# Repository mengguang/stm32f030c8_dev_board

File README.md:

# stm32f030c8_dev_board
stm32f030c8t6 development board.

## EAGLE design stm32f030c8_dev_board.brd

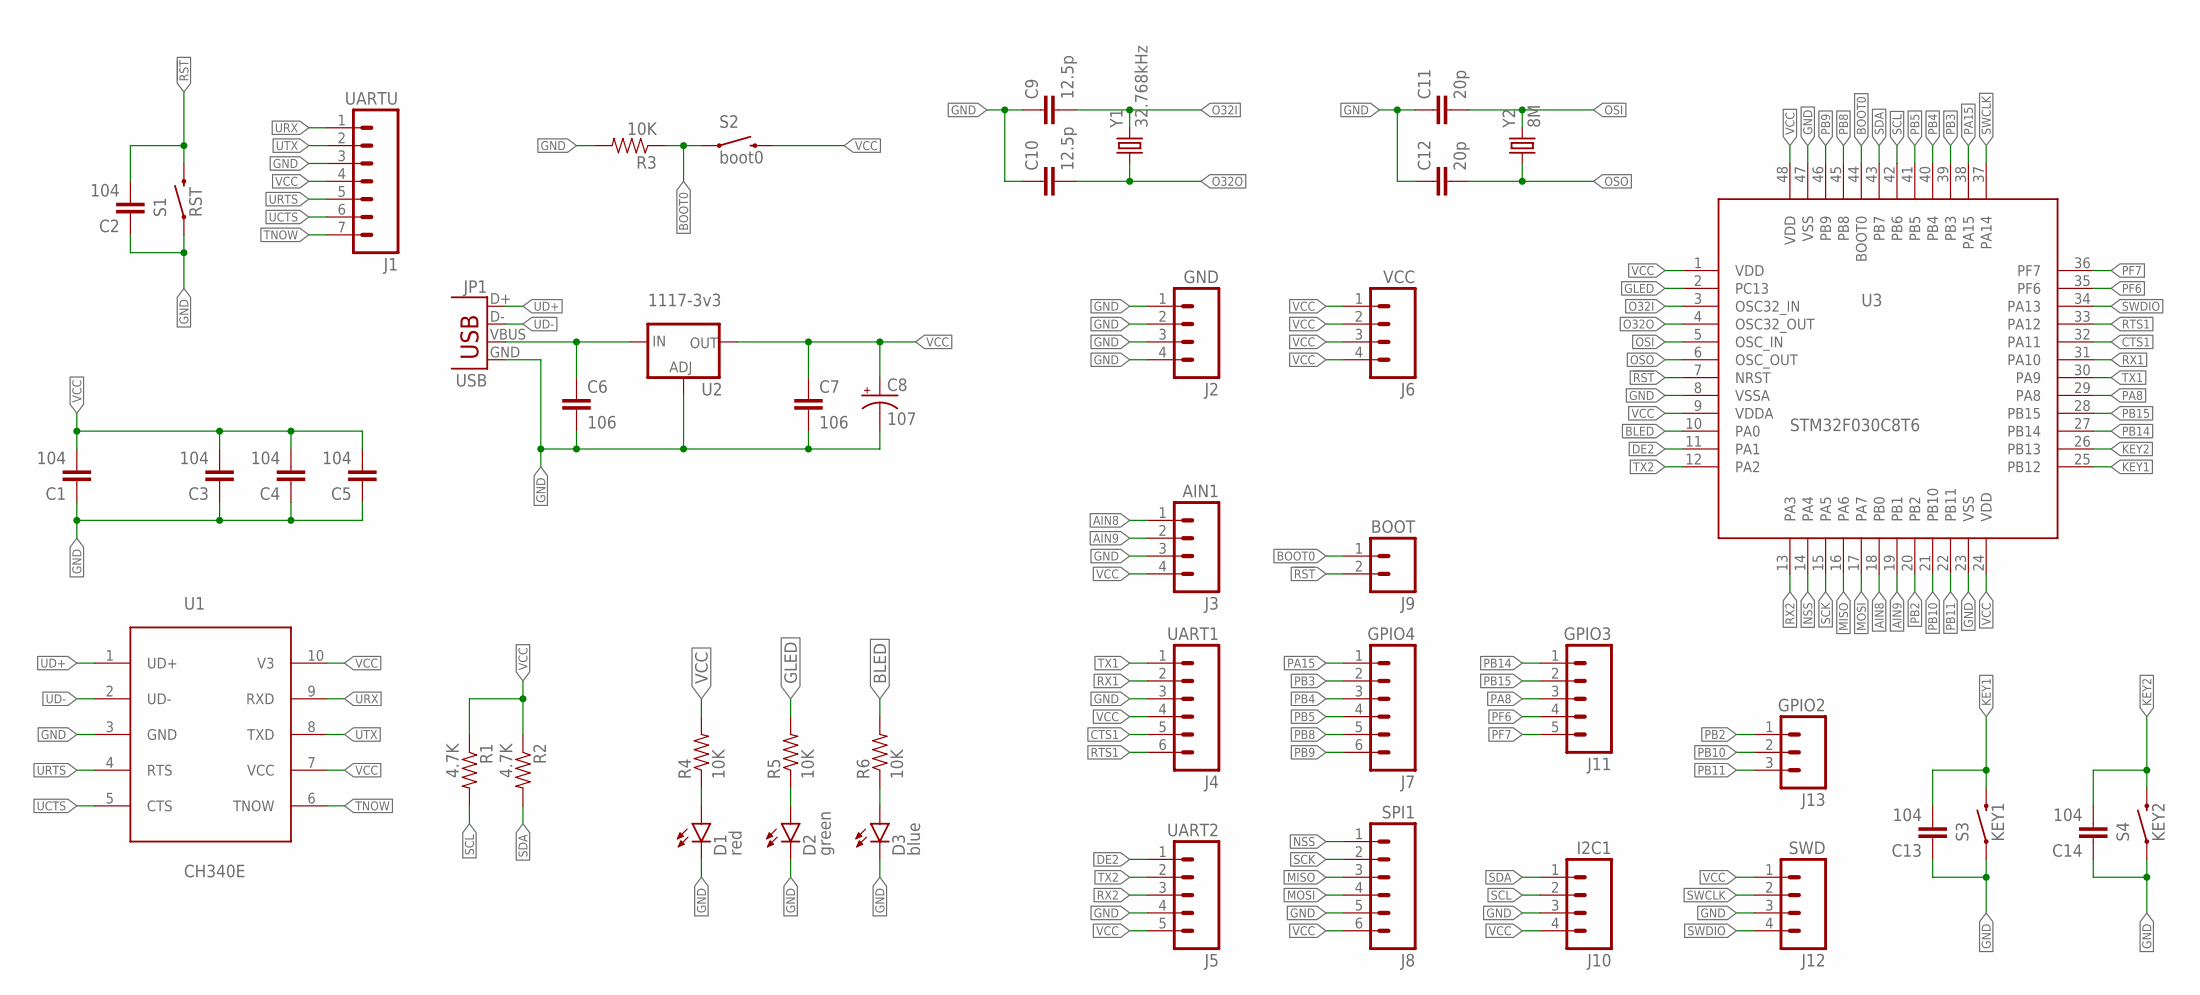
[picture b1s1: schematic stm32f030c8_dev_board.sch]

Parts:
C1, C2, C3, C4, C5, C13, C14: 104; C0402
C6, C7: 106; 0603-CAP
C8: 107; EIA3528
C9, C10: 12.5p; C0402
C11, C12: 20p; C0402
D1: red; LED-0603-SEEED
D2: green; LED-0603-SEEED
D3: blue; LED-0603-SEEED
J1: UARTU; 1X07_NO_SILK
J2: GND; 1X04_NO_SILK
J3: AIN1; 1X04_NO_SILK
J4: UART1; 1X06_NO_SILK
J5: UART2; 1X05_NO_SILK
J6: VCC; 1X04_NO_SILK
J7: GPIO4; 1X06_NO_SILK
J8: SPI1; 1X06_NO_SILK
J9: BOOT; 1X02_NO_SILK
J10: I2C1; 1X04_NO_SILK
J11: GPIO3; 1X05_NO_SILK
J12: SWD; 1X04_NO_SILK
J13: GPIO2; 1X03_NO_SILK
JP1: USB; MICROUSB-U-F-M5DD-Y-1
R1, R2: 4.7K; R0402
R3, R4, R5, R6: 10K; R0402
S1: RST; TACTILE-PTH
S2: boot0; TACTILE-PTH
S3: KEY1; TACTILE-PTH
S4: KEY2; TACTILE-PTH
U1: CH340E; MSOP10
U2: 1117-3v3; SOT223
U3: STM32F030C8T6; QFP50P900X900X160-48N
Y1: 32.768kHz; TC26H
Y2: 8M; HC49US

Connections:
!RST: C2.2, J9.2, S1.3 (2), U3.7 (NRST)
AIN8: J3.1, U3.18 (PB0)
AIN9: J3.2, U3.19 (PB1)
BLED: R6.2, U3.10 (PA0)
BOOT0: J9.1, R3.1, S2.1, U3.44 (BOOT0)
CTS1: J4.5, U3.32 (PA11)
DE2: J5.1, U3.11 (PA1)
GLED: R5.2, U3.2 (PC13)
GND: C1.1, C2.1, C3.1, C4.1, C5.1, C6.2, C7.2, C8.C (-), C9.1, C10.1, C11.1, C12.1, C13.1, C14.1, D1.- (C), D2.- (C), D3.- (C), J1.3, J2.1, J2.2, J2.3, J2.4, J3.3, J4.3, J5.4, J8.5, J10.3, J12.3, JP1.GND, R3.2, S1.1, S3.1, S4.1, U1.3 (GND), U2.1 (ADJ), U3.8 (VSSA), U3.23 (VSS), U3.47 (VSS)
KEY1: C13.2, S3.3 (2), U3.25 (PB12)
KEY2: C14.2, S4.3 (2), U3.26 (PB13)
MISO: J8.3, U3.16 (PA6)
MOSI: J8.4, U3.17 (PA7)
unnamed: D2.+ (A), R5.1
unnamed: D3.+ (A), R6.1
unnamed: D1.+ (A), R4.1
NSS: J8.1, U3.14 (PA4)
O32I: C9.2, U3.3 (OSC32_IN), Y1.2
O32O: C10.2, U3.4 (OSC32_OUT), Y1.1
OSI: C11.2, U3.5 (OSC_IN), Y2.2
OSO: C12.2, U3.6 (OSC_OUT), Y2.1
PA8: J11.3, U3.29 (PA8)
PA15: J7.1, U3.38 (PA15)
PB2: J13.1, U3.20 (PB2)
PB3: J7.2, U3.39 (PB3)
PB4: J7.3, U3.40 (PB4)
PB5: J7.4, U3.41 (PB5)
PB8: J7.5, U3.45 (PB8)
PB9: J7.6, U3.46 (PB9)
PB10: J13.2, U3.21 (PB10)
PB11: J13.3, U3.22 (PB11)
PB14: J11.1, U3.27 (PB14)
PB15: J11.2, U3.28 (PB15)
PF6: J11.4, U3.35 (PF6)
PF7: J11.5, U3.36 (PF7)
RTS1: J4.6, U3.33 (PA12)
RX1: J4.2, U3.31 (PA10)
RX2: J5.3, U3.13 (PA3)
SCK: J8.2, U3.15 (PA5)
SCL: J10.2, R1.2, U3.42 (PB6)
SDA: J10.1, R2.2, U3.43 (PB7)
SWCLK: J12.2, U3.37 (PA14)
SWDIO: J12.4, U3.34 (PA13)
TNOW: J1.7, U1.6 (TNOW)
TX1: J4.1, U3.30 (PA9)
TX2: J5.2, U3.12 (PA2)
UCTS: J1.6, U1.5 (CTS)
UD+: JP1.D+, U1.1 (UD+)
UD-: JP1.D-, U1.2 (UD-)
URTS: J1.5, U1.4 (RTS)
URX: J1.1, U1.9 (RXD)
UTX: J1.2, U1.8 (TXD)
VBUS: C6.1, JP1.VBUS, U2.3 (IN)
VCC: C1.2, C3.2, C4.2, C5.2, C7.1, C8.A (+), J1.4, J3.4, J4.4, J5.5, J6.1, J6.2, J6.3, J6.4, J8.6, J10.4, J12.1, R1.1, R2.1, R4.2, S2.3 (2), U1.7 (VCC), U1.10 (V3), U2.2 (OUT), U2.4 (OUT), U3.1 (VDD), U3.9 (VDDA), U3.24 (VDD), U3.48 (VDD)

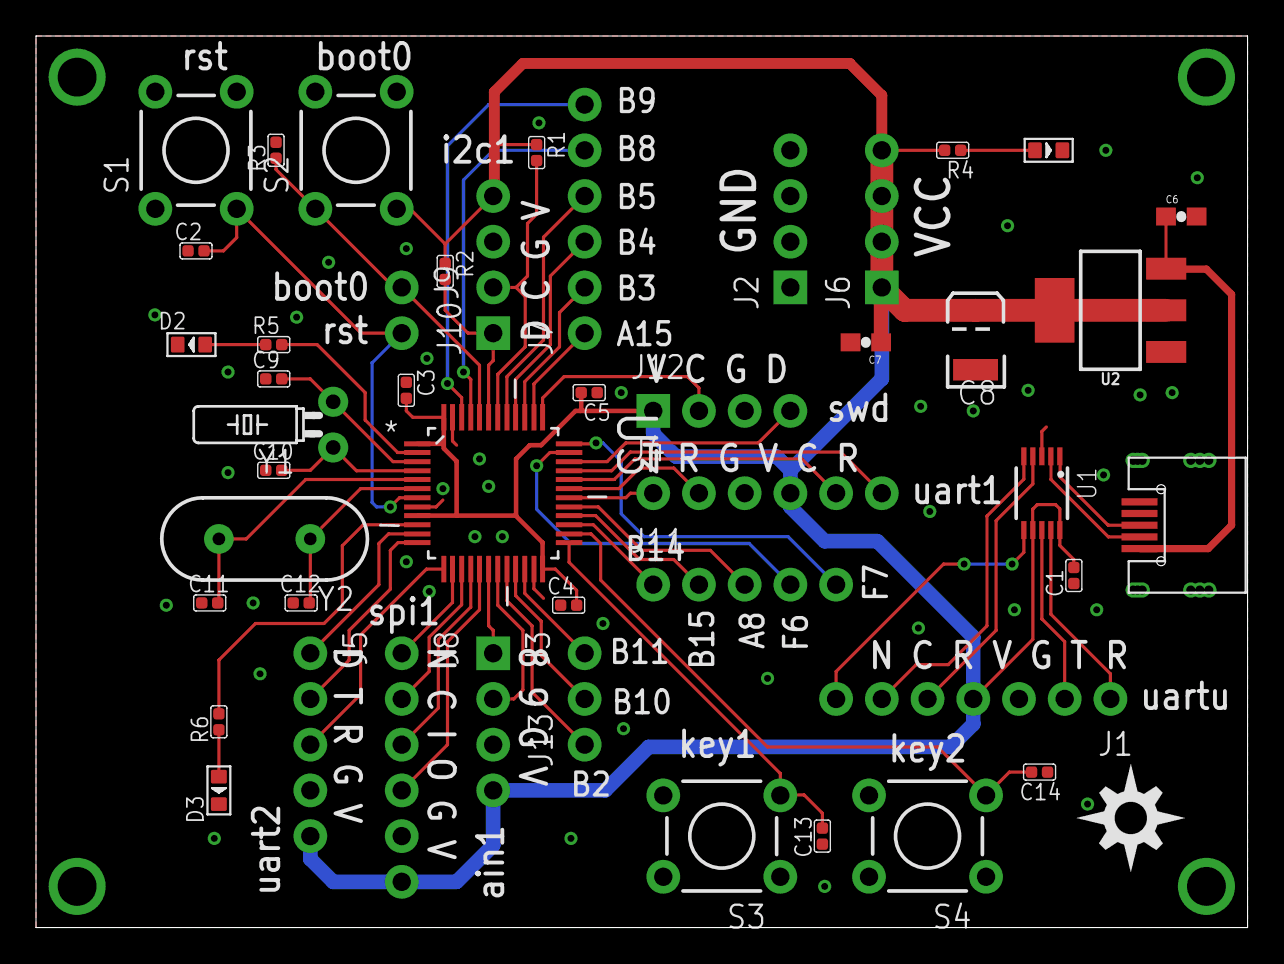
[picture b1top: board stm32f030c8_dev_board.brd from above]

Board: 2 copper layers, 67.3 x 49.5 mm, 47 parts (0 on the bottom side), 54 nets.

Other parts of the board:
U$1: DIYNOVA_LOGO

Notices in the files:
parts and their libraries:
SparkFun-Electromechanical: Licensing: Creative Commons ShareAlike 4.0 International - https://creativecommons.org/licenses/by-sa/4.0
